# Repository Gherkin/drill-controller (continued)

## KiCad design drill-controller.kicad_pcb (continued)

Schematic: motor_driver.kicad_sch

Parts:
C10: 100n 100V; C_0805_2012Metric; LCSC Part C28233
C11, C42, C43: 10u 50V; C_1206_3216Metric; LCSC Part C13585
C12, C44, C45: 100n 16V; C_0402_1005Metric; LCSC Part C1525
C13: 22n 50V; C_0603_1608Metric; LCSC Part C21122
C14: 10n; C_0402_1005Metric; LCSC Part C15195; not fitted
D9: RB751V-40; D_SOD-323; LCSC Part C7502691
R2: 0R; R_0402_1005Metric; LCSC Part C17168
R3, R7, R9: 10k 1%; R_0402_1005Metric; LCSC Part C25744
R4: 100k; R_0402_1005Metric; LCSC Part C25741
R5: 1k 1%; R_0402_1005Metric; LCSC Part C11702
R6, R8: 120k 1%; R_0402_1005Metric; LCSC Part C25750
R25: 330 1%; R_0402_1005Metric; LCSC Part C25104
TP13, TP14, TP15, TP16: TestPoint; TestPoint_THTPad_D1.0mm_Drill0.5mm
U5: DRV8874PWPR; HTSSOP-16_L5.0-W4.4-P0.65-LS6.4-BL-EP; LCSC Part C1855818

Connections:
+3V3: D9.1 (K), R3.1, U5.16 (PMODE); also elsewhere on the board
+24V: C10.1, C11.1, C12.1, C42.1, C43.1, U5.11 (VM); also elsewhere on the board
/Main Board/DRV_IN1: U5.1 (EN/IN1); also elsewhere on the board
/Main Board/DRV_IN2: U5.2 (PH/IN2); also elsewhere on the board
/Main Board/DRV_VREF: R4.1, TP14.1 (1_1), U5.5 (VREF); also elsewhere on the board
/Main Board/DRV_nFAULT: R3.2, U5.4 (nFAULT); also elsewhere on the board
/Main Board/DRV_nSLEEP: U5.3 (nSLEEP); also elsewhere on the board
/Main Board/IPROPI: C14.1, D9.2 (A), R5.1, TP13.1 (1_1), U5.6 (IPROPI); also elsewhere on the board
/Main Board/MOTOR_A: R6.1, TP15.1 (1_1), U5.8 (OUT1); also elsewhere on the board
/Main Board/MOTOR_B: R8.1, TP16.1 (1_1), U5.10 (OUT2); also elsewhere on the board
/Main Board/MOT_V1: C44.1, R6.2, R7.1; also elsewhere on the board
/Main Board/MOT_V2: C45.1, R8.2, R9.1; also elsewhere on the board
/Main Board/Motor Driver/CPH: C13.1, U5.13 (CPH)
/Main Board/Motor Driver/CPL: C13.2, U5.14 (CPL)
/Main Board/Motor Driver/IMODE: R2.1, U5.7 (IMODE)
/Main Board/Motor Driver/VCP: C12.2, U5.12 (VCP)
GND: C10.2, C11.2, C14.2, C42.2, C43.2, C44.2, C45.2, R2.2, R4.2, R7.2, R9.2, R25.2, U5.9 (PGND), U5.15 (GND), U5.17 (EP); also elsewhere on the board
unnamed: R5.2, R25.1

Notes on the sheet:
D9 clamps IPROPI to +3V3 (#33). Layout: put D9 next to U2 pin 9 (PA1). Short traces to PA1 and to +3V3.
Layout: the motor path carries up to 5.2 A (cold stall and brake, plan sections 2 and 4.6, #84): +24V to U5 pin 11 (VM), U5 pins 8/10 (OUT1/OUT2) -> MOTOR_A/MOTOR_B -> J3 (main board), and U5 pin 9 (PGND) back to GND. Size these like the #63 input path: pours, or traces at least 3 mm wide on 1 oz o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
C42, C43, C11 carry the PWM ripple current on VM (#34). Layout: put C42, C43, C11 right at U5 pin 11 (VM), shortest loop to U5 pin 9 (PGND). C21 can take only ~0.17 A rms. Layout (#85): C10 (100 nF) also at U5 pin 11, closest to the pin, with C11, C42, C43 (10 µF) just behind it. C12 (VCP-VM, 100 n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
C44/C45 average the PWM on MOT_V1/MOT_V2 for the ADC (#48). Layout: C44 next to U2 pin 16 (PB0), C45 next to U2 pin 17 (PB1).
Layout: U5 EP pad 17 to a top GND pour of at least 16 cm² (2-layer), plus a bottom GND pour under U5 joined by the EP thermal vias (#83). D56 p31: maximize the copper on the thermal pad. The plan 4.4 continuous limit (#40) assumes this: 2-layer 1 oz R_θJA 63 °C/W at 4 cm², 44 °C/W at 16 cm² (D56 p2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
Layout: TP13-TP16 are bring-up test pads, not fitted (#36). TP13 (IPROPI) next to R5. TP15/TP16 on the OUT1/OUT2 copper, not on a thin stub.
Layout: U5 EP pad 17 has 4 GND vias (0.3 mm drill) inside the EP copper (#77). Top: under F.Paste and the F.Mask opening. Bottom: tented (no B.Mask opening). D56 p40 note 9: vias under paste should be filled, plugged or tented. Before fab: order plugged/filled vias, or split the EP paste into windo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

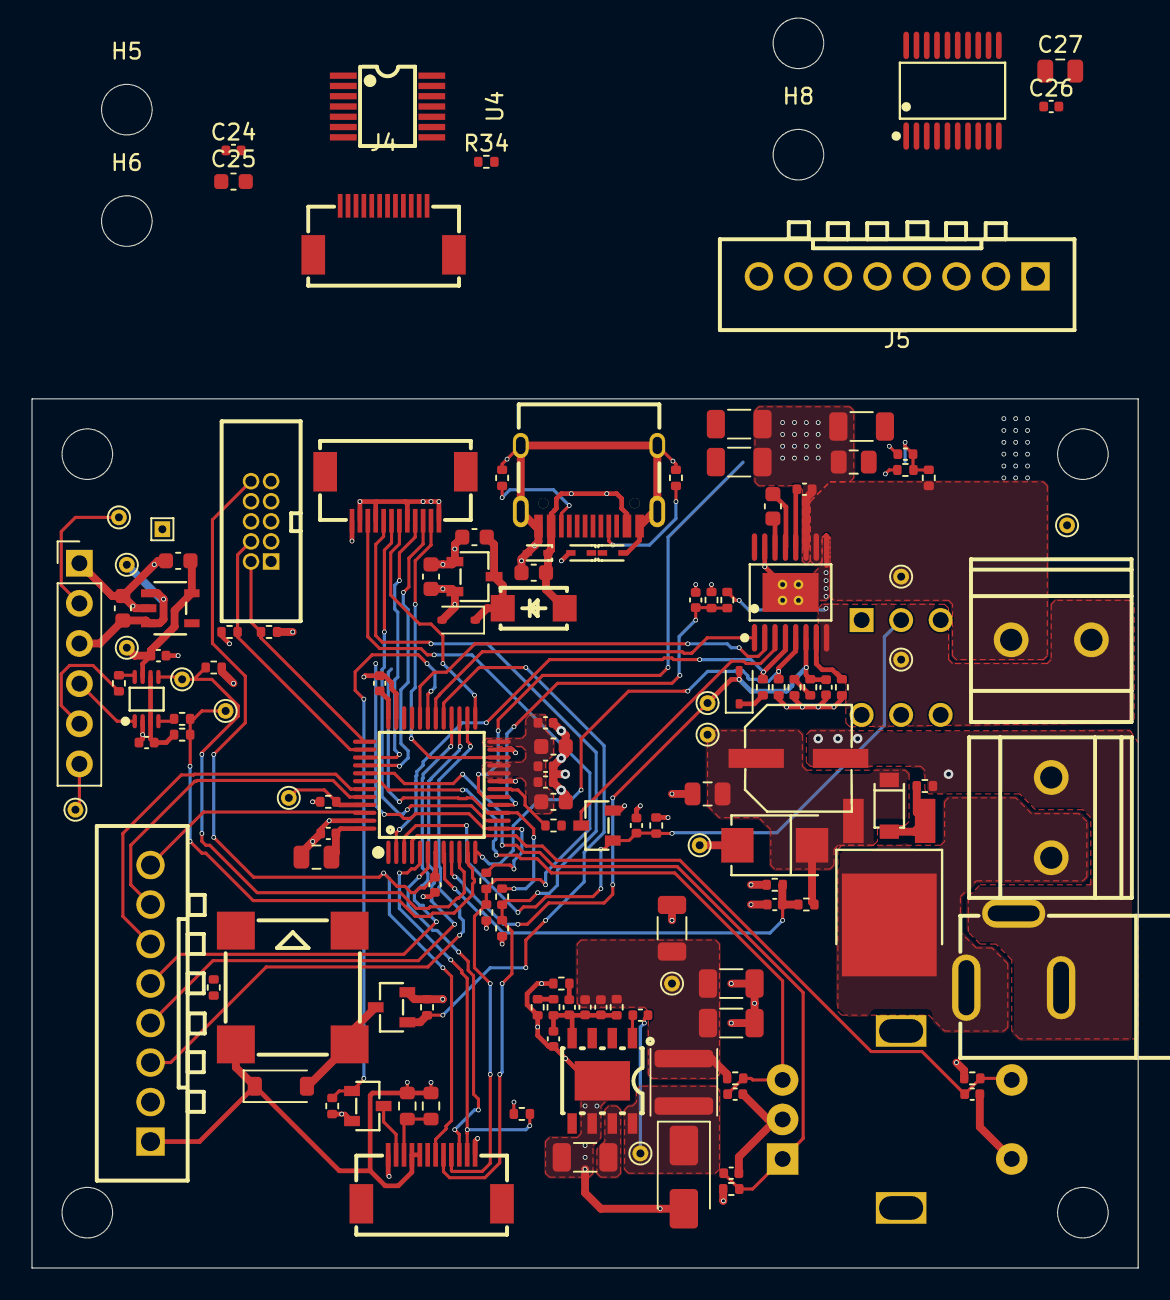
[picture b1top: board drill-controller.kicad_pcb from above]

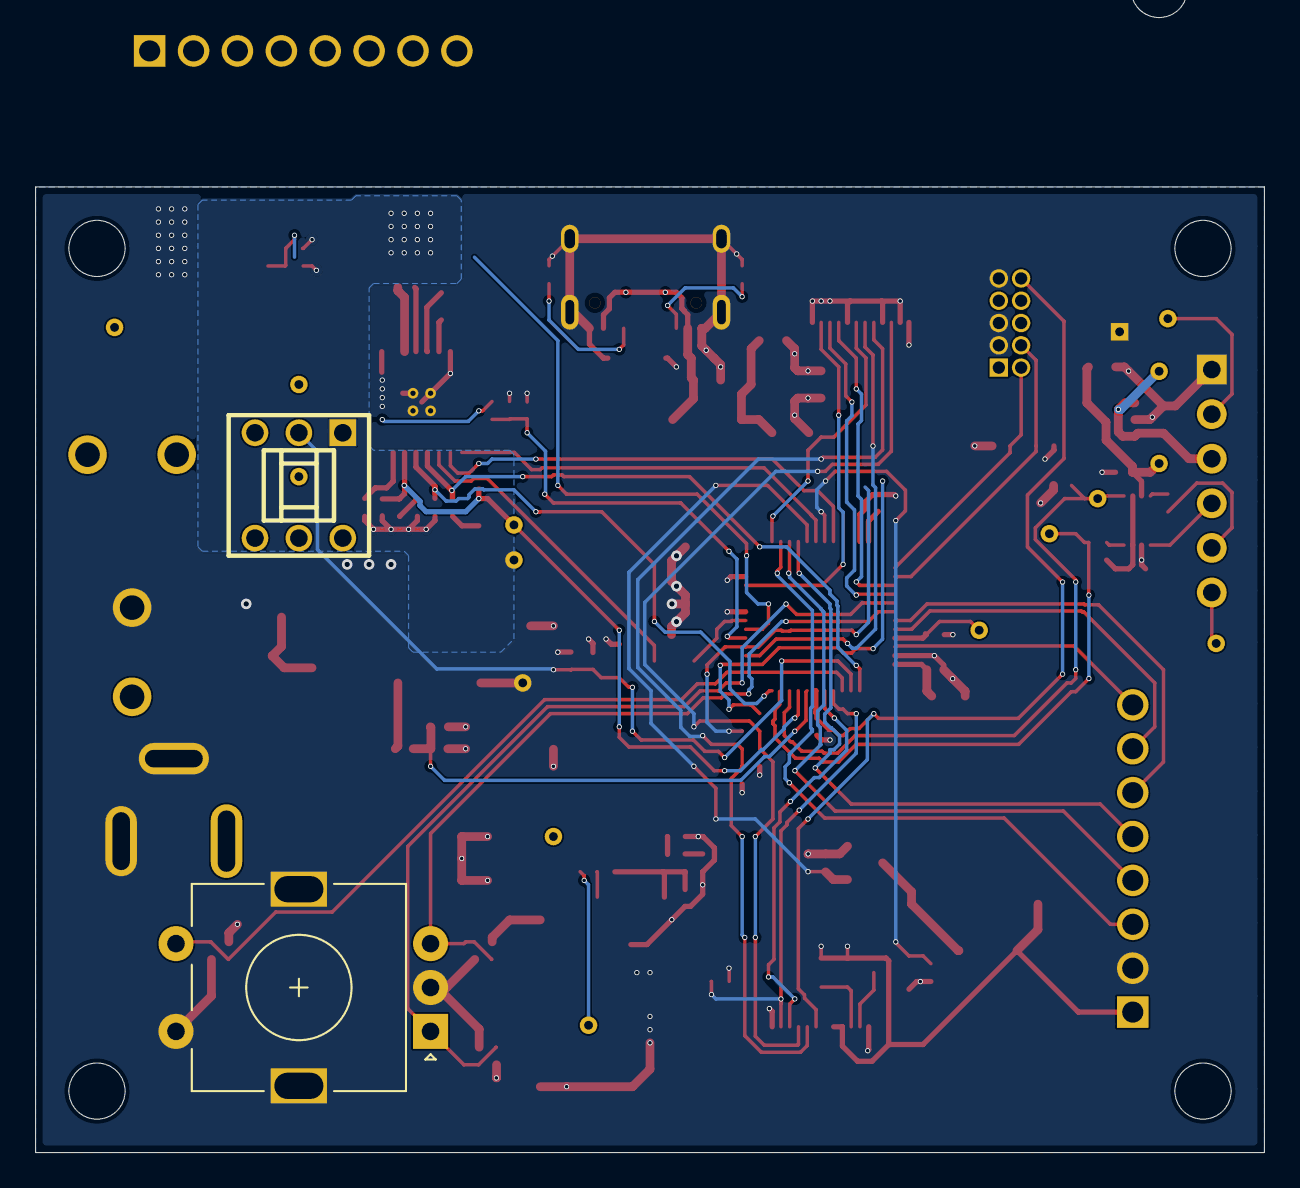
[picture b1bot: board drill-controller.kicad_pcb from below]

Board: 4 copper layers, 70.0 x 55.0 mm, 147 parts (2 on the bottom side), 90 nets.
